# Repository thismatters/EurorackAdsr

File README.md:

# ADSR

```
   /\D
 A/  \_____
 /      S  \R
/           \
```

An envelope generator with classic ADSR profile centered around the 555 timer, responsive to a gate input. Adjustable durations for attack, duration, and release; and adjustable voltage for the sustain portion.

The circuit here is based on the [Yusynth ADSR (newer version)](https://yusynth.net/Modular/EN/ADSR/index_latest.html) with minor tweaks to make it more Eurorack friendly. The changes I've made are thus:
* Selected resistors appropriate for +/-12V rails,
* Added polarity protection so that a backward power header doesn't fry anything (twin series schotty diodes: BAT54SL),
* Full surface mount design.

The Yusynth page is a treasure trove of information about this circuit that I am too amateur to claim as my own; please read that outstanding page before using this circuit. The page provides many details and other implementations of this circuit that you may find suitable.

The KiCAD project here uses the library/footprints [found in my companion repo](https://github.com/thismatters/EurorackKiCAD).

## Width

6hp on a standard 3U rack.

## Inputs

Accepts gate input via patch cable, has pushbutton for manual gating.
Four knobs set the shape of the envelope. A toggle switch sets the response of the envelope generator between fast and slow.

## Outputs

Envelope and inverted envelope outputs. LED visualizes the output signal.

## Vendors

There are part numbers in the [BOM](adsr.csv) for many of the parts (not for basic passives though) at the following vendors:

* [Mouser](https://www.mouser.com): Needs no introduction. Get your ICs from here (or [digikey](https://www.digikey.com)).
* [Tayda Electronics](https://www.taydaelectronics.com/): Good supplier for passive components; audio jacks, and potentiometers. Their audio jacks are slightly smaller than the thonkiconn from thonk.
* [Love My Switches](https://lovemyswitches.com/): Has [really good knobs](https://lovemyswitches.com/anodized-aluminum-knob-the-lo-fi-1-4-smooth-shaft-12-5mm-od/) to go on those potentiometers!
* [OSHPark](https://oshpark.com/): Fast and (relatively) cheap PCB manufacturer. [V2 board](https://oshpark.com/shared_projects/UEztaF3P) works great!

## Changelog

### V2

* Fixed decay/sustain relation (swapped terminals of op amp U2(C))
* Fixed direction of decay potentiometer (swapped pins 1 and 3 of RV3)
* Fixed polarity of tantalum capacitors
* Bigger hole for LED bezel
* Fixed part number for NPN transistors

### V3 (unreleased)

* new design language

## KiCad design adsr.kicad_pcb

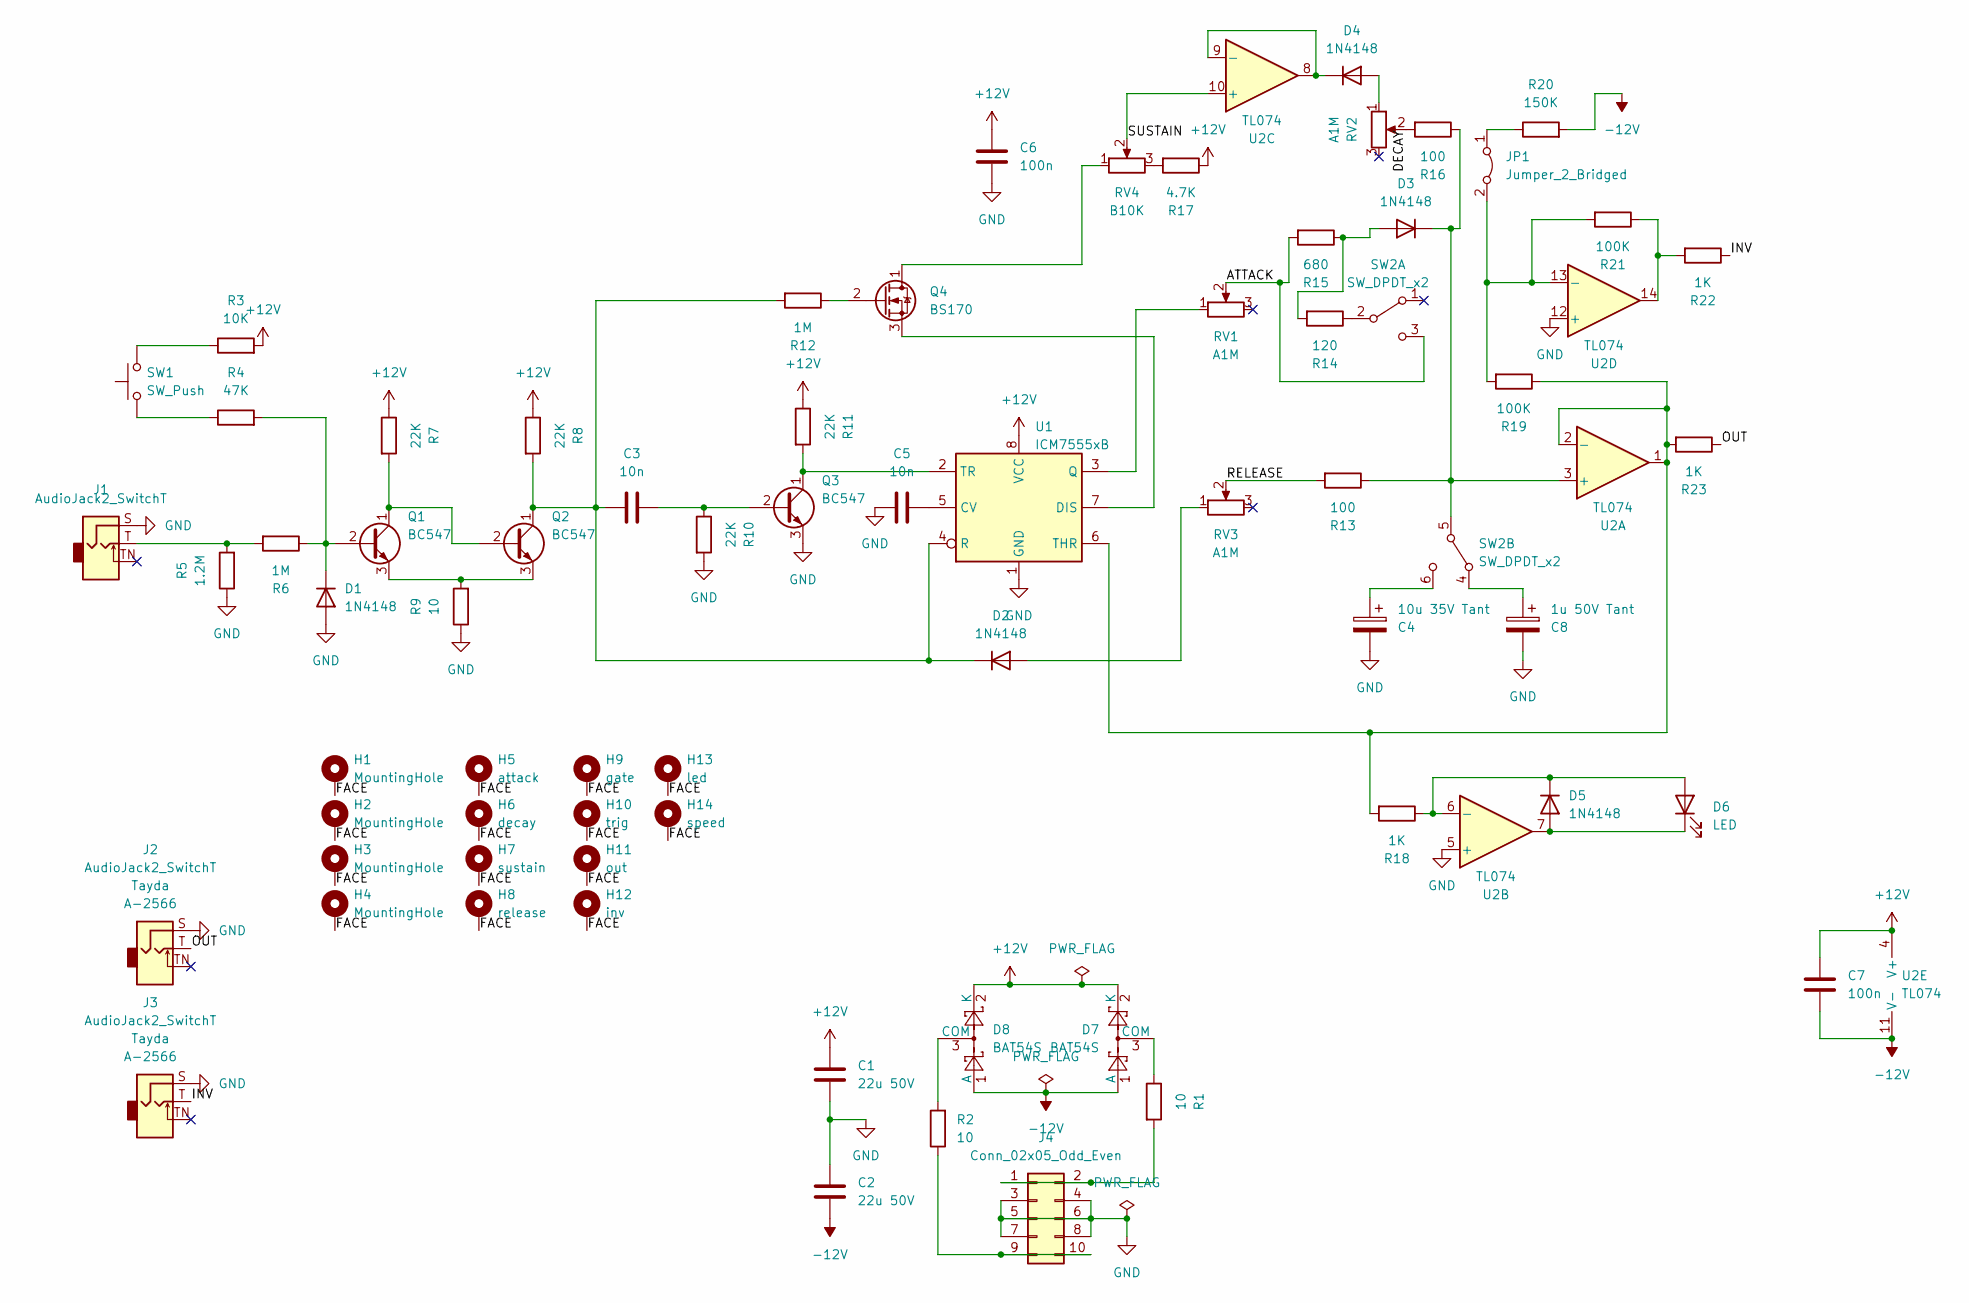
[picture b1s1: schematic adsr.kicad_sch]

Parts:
C1, C2: 22u 50V; CP_Radial_D5.0mm_P2.50mm
C3, C5: 10n; C_0805_2012Metric
C4: 10u 35V Tant; CP_Radial_D5.0mm_P2.50mm
C6, C7: 100n; C_0805_2012Metric
C8: 1u 50V Tant; CP_Radial_D5.0mm_P2.50mm
D1, D2, D3, D4, D5: 1N4148; D_SOD-323_HandSoldering
D6: LED; LED_D3.0mm
D7, D8: BAT54S; SOT-23; PartNum 863-BAT54SLT1G
H1, H2, H3, H4: MountingHole; Mech-MountingHole
H5: attack; Mech-Potentiometer-Hole_level
H6: decay; Mech-Potentiometer-Hole_level
H7: sustain; Mech-Potentiometer-Hole_level
H8: release; Mech-Potentiometer-Hole_level
H9: gate; Mech-AudioJack-Hole-Input-Gate
H10: trig; Mech-PushButton-Hole_Tayda_A-5051
H11: out; Mech-AudioJack-Hole-Output-CV
H12: inv; Mech-AudioJack-Hole-Output-CV
H13: led; Mech-LED-Hole-3mm-Bezel
H14: speed; Mech-2M_Switch-Hole
J1, J2, J3: AudioJack2_SwitchT; AudioJack2_Tayda_A-2566; PartNum A-2566
J4: Conn_02x05_Odd_Even; PinHeader_2x05_P2.54mm_Vertical; PartNum A-2939
JP1: Jumper_2_Bridged; PinHeader_1x02_P2.54mm_Vertical
Q1, Q2, Q3: BC547; TO-92L_Inline_Wide; PartNum 637-BC547C
Q4: BS170; TO-92_Inline; PartNum 512-BS170
R1, R2, R9: 10; R_0805_2012Metric
R3: 10K; R_0805_2012Metric
R4: 47K; R_0805_2012Metric
R5: 1.2M; R_0805_2012Metric
R6, R12: 1M; R_0805_2012Metric
R7, R8, R10, R11: 22K; R_0805_2012Metric
R13, R16: 100; R_0805_2012Metric
R14: 120; R_0805_2012Metric
R15: 680; R_0805_2012Metric
R17: 4.7K; R_0805_2012Metric
R18, R22, R23: 1K; R_0805_2012Metric
R19, R21: 100K; R_0805_2012Metric
R20: 150K; R_0805_2012Metric
RV1, RV2, RV3: A1M; Potentiometer_RV16AF-41-15R1; PartNum A-2425
RV4: B10K; Potentiometer_RV16AF-41-15R1; PartNum A-2969
SW1: SW_Push; PushButton_Tayda_A-5051; PartNum A-5051
SW2: SW_DPDT_x2; Switch_DPDT_Tayda_A-5752; PartNum A-6809
U1: ICM7555xB; SOIC-8_3.9x4.9mm_P1.27mm; PartNum 968-ICM7555CBAZ-T
U2: TL074; SOIC-14_3.9x8.7mm_P1.27mm; PartNum 595-TL074CN

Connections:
+12V: C1.1, C6.1, C7.1, D7.2 (K), D8.2 (K), R3.2, R7.1, R8.1, R11.1, R17.1, U1.8 (VCC), U2.4 (V+)
-12V: C2.2, C7.2, D7.1 (A), D8.1 (A), R20.2, U2.11 (V-)
/ATTACK: R15.2, RV1.2, SW2.3 (C)
/DECAY: R16.2, RV2.2
/FACE: H1.1, H2.1, H3.1, H4.1, H5.1, H6.1, H7.1, H8.1, H9.1, H10.1, H11.1, H12.1, H13.1, H14.1
/INV: J3.T, R22.1
/OUT: J2.T, R23.1
/RELEASE: R13.2, RV3.2
/SUSTAIN: RV4.2, U2.10 (+)
GND: C1.2, C2.1, C4.2, C5.1, C6.2, C8.2, D1.2 (A), J1.S, J2.S, J3.S, J4.3, J4.4, J4.5, J4.6, J4.7, J4.8, Q3.3 (E), R5.1, R9.1, R10.2, U1.1 (GND), U2.5 (+), U2.12 (+)
unnamed: D1.1 (K), Q1.2 (B), R4.2, R6.1
unnamed: D2.2 (A), RV3.1
unnamed: C3.1, D2.1 (K), Q2.1 (C), R8.2, R12.2, U1.4 (R)
unnamed: D3.2 (A), R14.2, R15.1
unnamed: D3.1 (K), R13.1, R16.1, SW2.5 (B), U2.3 (+)
unnamed: D4.2 (A), RV2.1
unnamed: D4.1 (K), U2.8, U2.9 (-)
unnamed: D5.2 (A), D6.1 (K), U2.7
unnamed: D5.1 (K), D6.2 (A), R18.1, U2.6 (-)
unnamed: D7.3 (COM), R1.1
unnamed: D8.3 (COM), R2.2
unnamed: J1.T, R5.2, R6.2
unnamed: J4.1, J4.2, R1.2
unnamed: J4.9, J4.10, R2.1
unnamed: JP1.1 (A), R20.1
unnamed: JP1.2 (B), R19.2, R21.2, U2.13 (-)
unnamed: Q1.1 (C), Q2.2 (B), R7.2
unnamed: Q1.3 (E), Q2.3 (E), R9.2
unnamed: C3.2, Q3.2 (B), R10.1
unnamed: Q3.1 (C), R11.2, U1.2 (TR)
unnamed: Q4.1 (D), RV4.1
unnamed: Q4.2 (G), R12.1
unnamed: Q4.3 (S), U1.7 (DIS)
unnamed: R3.1, SW1.2
unnamed: R4.1, SW1.1
unnamed: R17.2, RV4.3
unnamed: R21.1, R22.2, U2.14
unnamed: R14.1, SW2.2 (B)
unnamed: C8.1, SW2.4 (A)
unnamed: C4.1, SW2.6 (C)
unnamed: C5.2, U1.5 (CV)
unnamed: RV1.1, U1.3 (Q)
unnamed: R18.2, R19.1, R23.2, U1.6 (THR), U2.1, U2.2 (-)

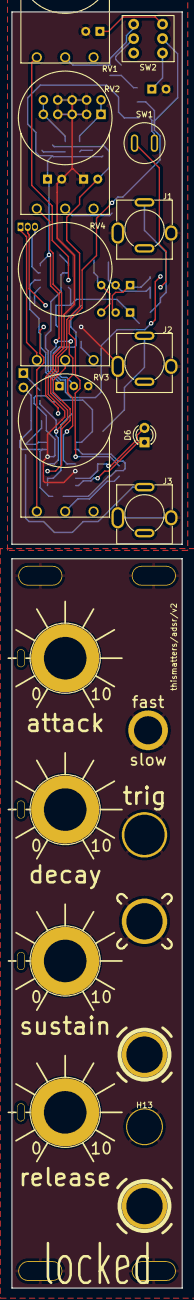
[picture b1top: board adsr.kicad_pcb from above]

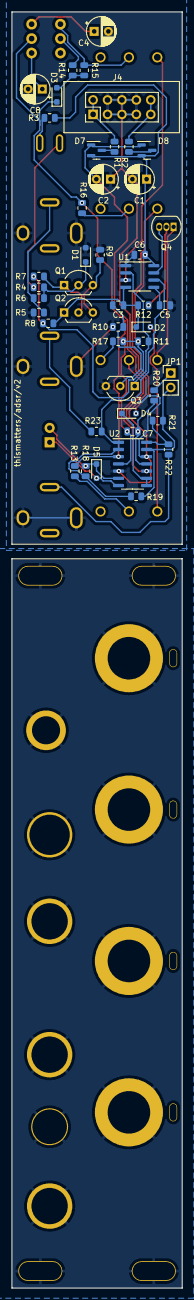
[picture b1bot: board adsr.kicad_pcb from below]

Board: 2 copper layers, 30.0 x 224.8 mm, 70 parts (46 on the bottom side), 43 nets.

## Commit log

2024-01-03 getting started
2024-01-03 first draft pcb
2024-01-04 slightly more compact pcb
2024-01-15 prepped for manu
2024-01-15 adding readme
2024-01-15 better bom
2024-01-15 removing non-parts from BOM
2024-03-03 v2 fixes
2024-07-29 updating BOM for v2
2024-11-24 new design language, adding pcb to readme
2026-01-19 add gitignore
